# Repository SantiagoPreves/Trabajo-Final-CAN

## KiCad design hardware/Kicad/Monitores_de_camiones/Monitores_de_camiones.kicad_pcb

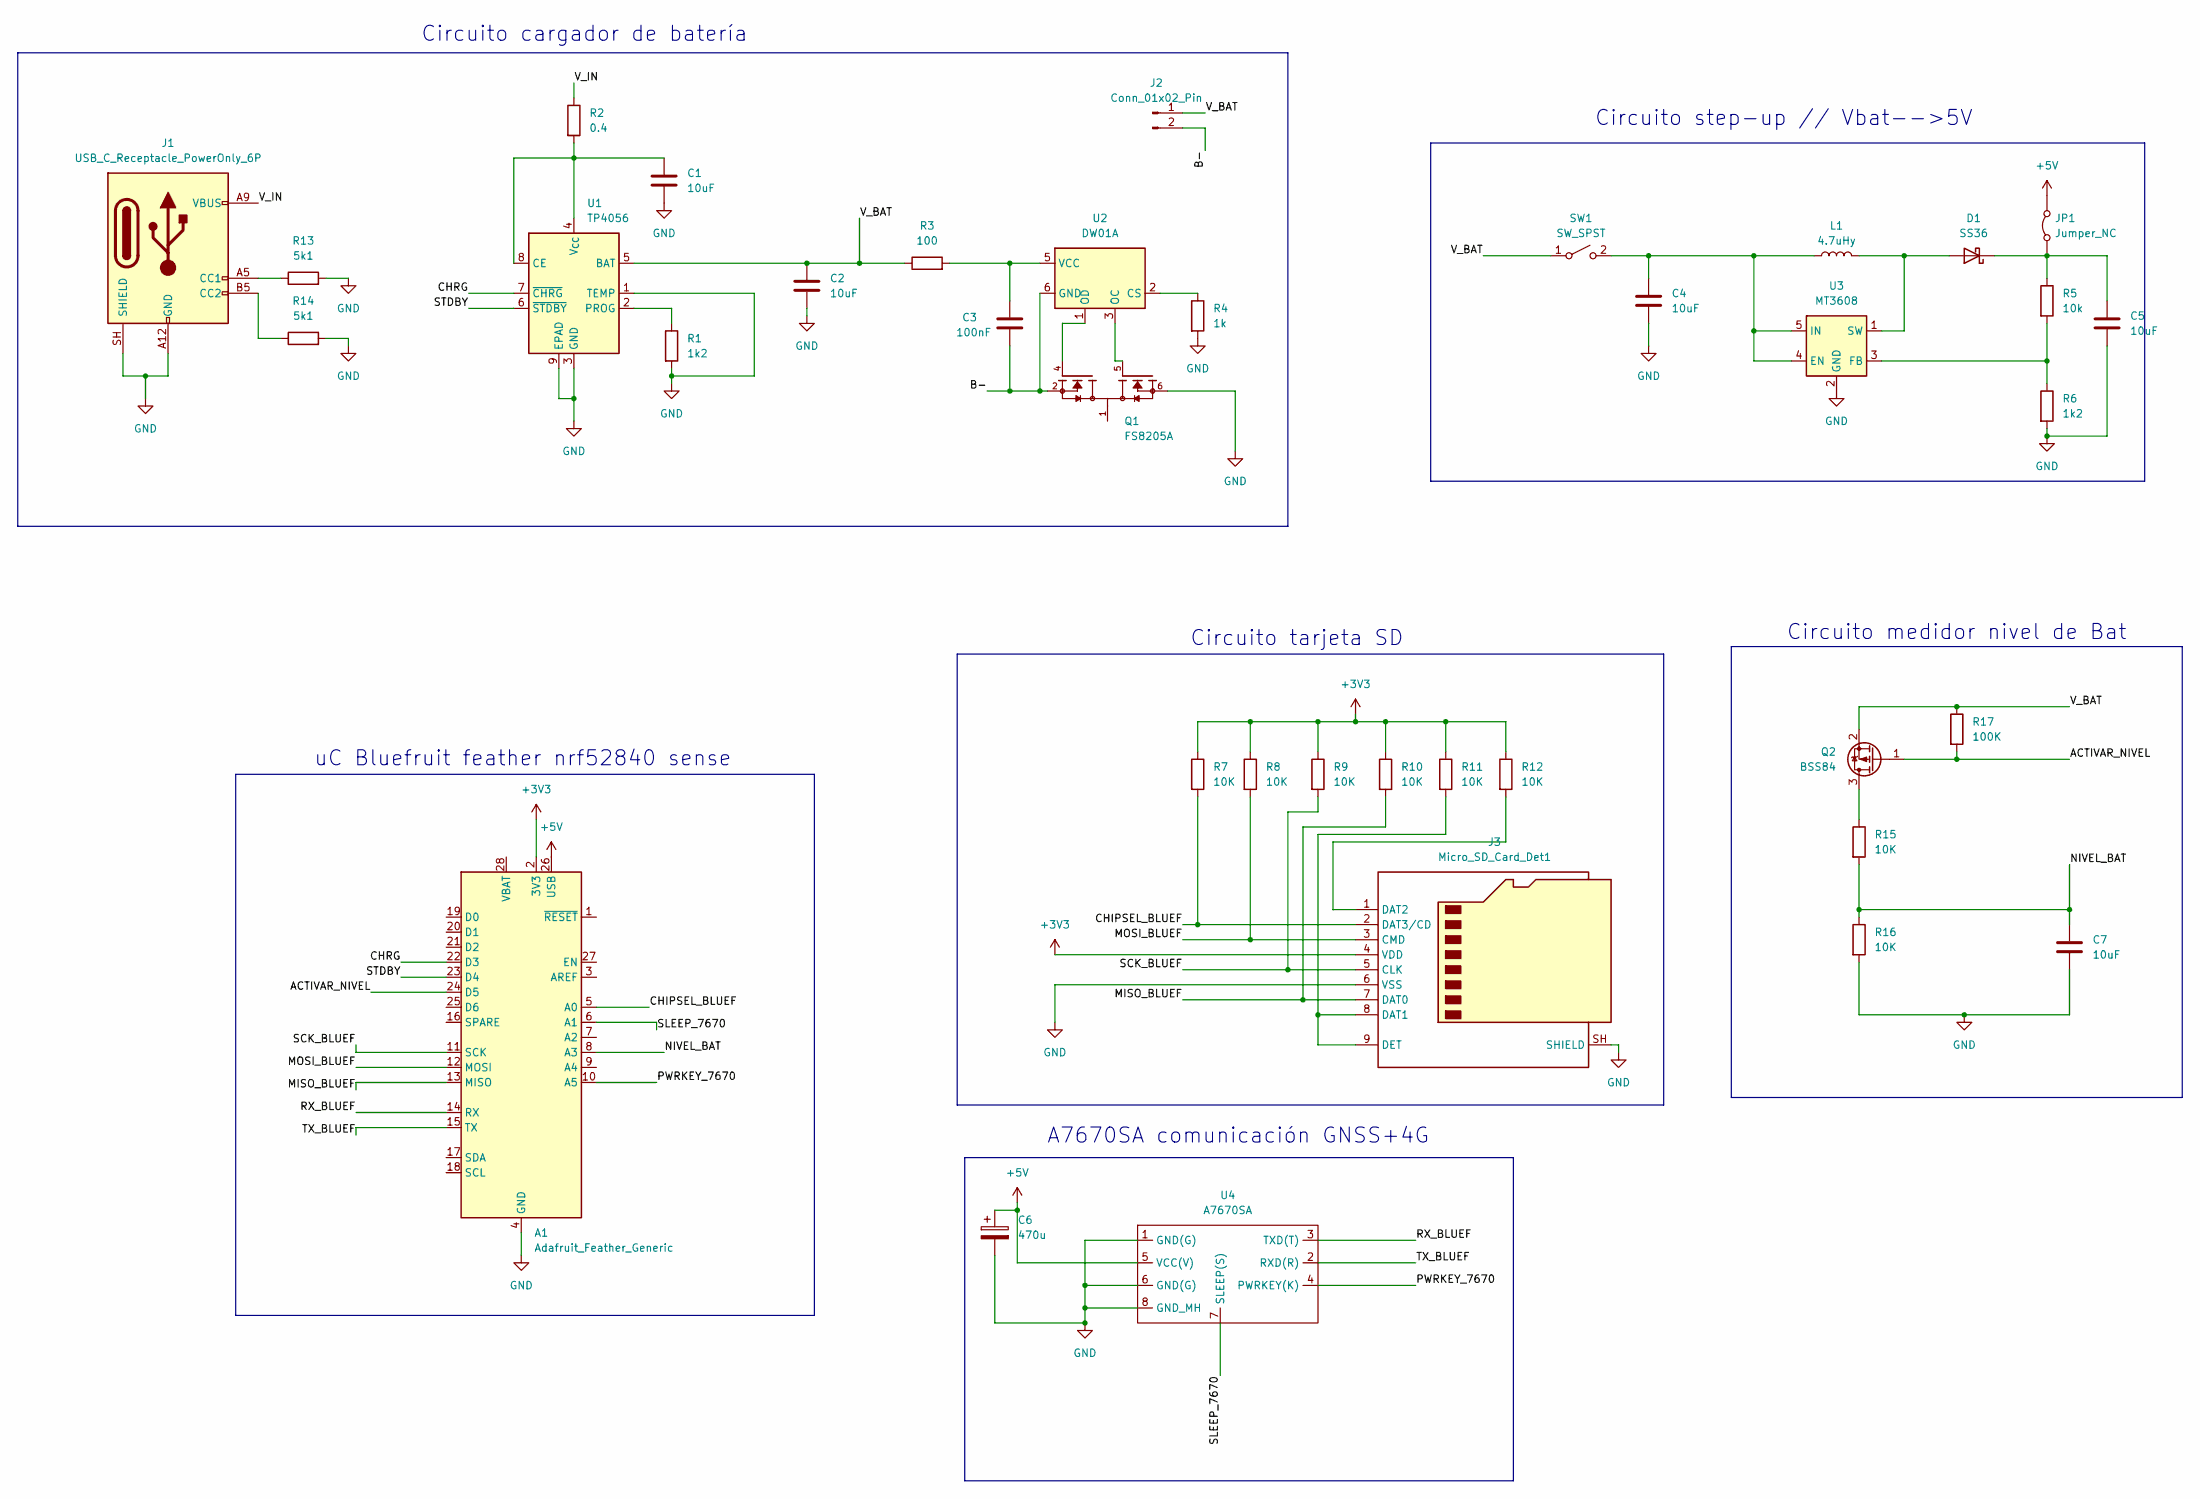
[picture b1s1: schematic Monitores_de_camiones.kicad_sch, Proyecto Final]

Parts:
A1: Adafruit_Feather_Generic; Adafruit_Feather
C1, C2, C7: 10uF; C_0805_2012Metric_Pad1.18x1.45mm_HandSolder
C3: 100nF; C_0805_2012Metric_Pad1.18x1.45mm_HandSolder
C4, C5: 10uF; C_1206_3216Metric_Pad1.33x1.80mm_HandSolder
C6: 470u; CP_Elec_6.3x5.2
D1: SS36; D_SMA
J1: USB_C_Receptacle_PowerOnly_6P; USB_C_Receptacle_GCT_USB4125-xx-x-0190_6P_TopMnt_Horizontal
J2: Conn_01x02_Pin; Molex_KK-254_AE-6410-02A_1x02_P2.54mm_Vertical
J3: Micro_SD_Card_Det1; microSD_HC_Hirose_DM3AT-SF-PEJM5
JP1: Jumper_NC; PinHeader_1x02_P2.54mm_Vertical
L1: 4.7uHy; L_Wuerth_WE-PDF_Handsoldering
Q1: FS8205A; FS8205A_TSSOP-8; PARTREV 1.7
Q2: BSS84; SOT-23
R1, R6: 1k2; R_0805_2012Metric_Pad1.20x1.40mm_HandSolder
R2: 0.4; R_0805_2012Metric_Pad1.20x1.40mm_HandSolder
R3: 100; R_0805_2012Metric_Pad1.20x1.40mm_HandSolder
R4: 1k; R_0805_2012Metric_Pad1.20x1.40mm_HandSolder
R5: 10k; R_0805_2012Metric_Pad1.20x1.40mm_HandSolder
R7, R8, R9, R10, R11, R12, R15, R16: 10K; R_0805_2012Metric_Pad1.20x1.40mm_HandSolder
R13, R14: 5k1; R_0805_2012Metric_Pad1.20x1.40mm_HandSolder
R17: 100K; R_0805_2012Metric_Pad1.20x1.40mm_HandSolder
SW1: SW_SPST; PinHeader_1x02_P2.54mm_Vertical
U1: TP4056; SOIC-8-1EP_3.9x4.9mm_P1.27mm_EP2.41x3.3mm_ThermalVias
U2: DW01A; SOT-23-6
U3: MT3608; SOT-23-6
U4: A7670SA

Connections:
+3V3: A1.2 (3V3), J3.4 (VDD), R7.1, R8.1, R9.1, R10.1, R11.1, R12.1
+5V: A1.26 (USB), C6.1, JP1.2 (B), U4.5 (VCC(V))
/ACTIVAR_NIVEL: A1.24 (D5), Q2.1 (G), R17.2
/B-: C3.2, J2.2, Q1.2, Q1.3, U2.6 (GND)
/CHIPSEL_BLUEF: A1.5 (A0), J3.2 (DAT3/CD), R7.2
/CHRG: A1.22 (D3), U1.7 (~CHRG)
/MISO_BLUEF: A1.13 (MISO), J3.7 (DAT0), R10.2
/MOSI_BLUEF: A1.12 (MOSI), J3.3 (CMD), R8.2
/NIVEL_BAT: A1.8 (A3), C7.1, R15.2, R16.1
/PWRKEY_7670: A1.10 (A5), U4.4 (PWRKEY(K))
/RX_BLUEF: A1.14 (RX), U4.3 (TXD(T))
/SCK_BLUEF: A1.11 (SCK), J3.5 (CLK), R9.2
/SLEEP_7670: A1.6 (A1), U4.7 (SLEEP(S))
/STDBY: A1.23 (D4), U1.6 (~STDBY)
/TX_BLUEF: A1.15 (TX), U4.2 (RXD(R))
/V_BAT: C2.1, J2.1, Q2.2 (S), R3.1, R17.1, SW1.1 (A), U1.5 (BAT)
/V_IN: J1.A9 (VBUS), J1.B9 (VBUS), R2.1
GND: A1.4 (GND), C1.2, C2.2, C4.2, C5.2, C6.2, C7.2, J1.A12 (GND), J1.B12 (GND), J1.SH (SHIELD), J3.6 (VSS), J3.SH (SHIELD), Q1.6, Q1.7, R1.2, R4.2, R6.2, R13.2, R14.2, R16.2, U1.1 (TEMP), U1.3 (GND), U1.9 (EPAD), U3.2 (GND), U4.1 (GND(G)), U4.6 (GND(G)), U4.8 (GND_MH)
unnamed: D1.2 (A), L1.2, U3.1 (SW)
unnamed: C5.1, D1.1 (K), JP1.1 (A), R5.1
unnamed: J1.A5 (CC1), R13.1
unnamed: J1.B5 (CC2), R14.1
unnamed: J3.8 (DAT1), J3.9 (DET), R11.2
unnamed: J3.1 (DAT2), R12.2
unnamed: Q1.1, Q1.8
unnamed: Q2.3 (D), R15.1
unnamed: C4.1, L1.1, SW1.2 (B), U3.4 (EN), U3.5 (IN)
unnamed: C1.1, R2.2, U1.4 (V_{CC}), U1.8 (CE)
unnamed: R1.1, U1.2 (PROG)
unnamed: R4.1, U2.2 (CS)
unnamed: Q1.5, U2.3 (OC)
unnamed: Q1.4, U2.1 (OD)
unnamed: C3.1, R3.2, U2.5 (VCC)
unnamed: R5.2, R6.1, U3.3 (FB)

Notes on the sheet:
A7670SA comunicación GNSS+4G
Circuito tarjeta SD
Circuito cargador de batería
Circuito medidor nivel de Bat
Circuito step-up // Vbat-->5V
uC Bluefruit feather nrf52840 sense

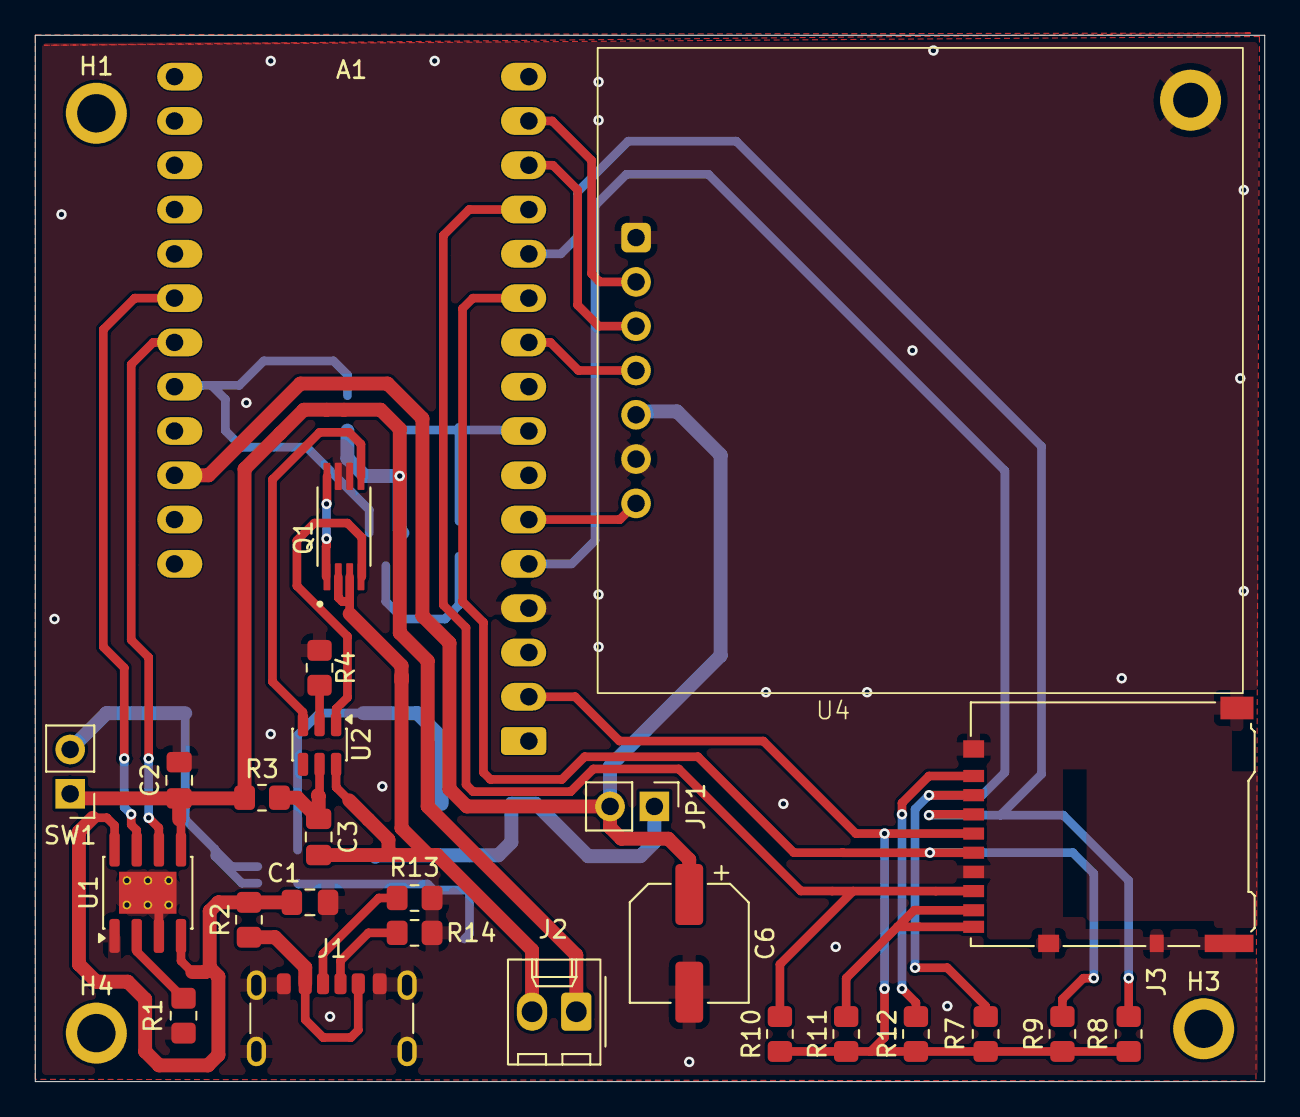
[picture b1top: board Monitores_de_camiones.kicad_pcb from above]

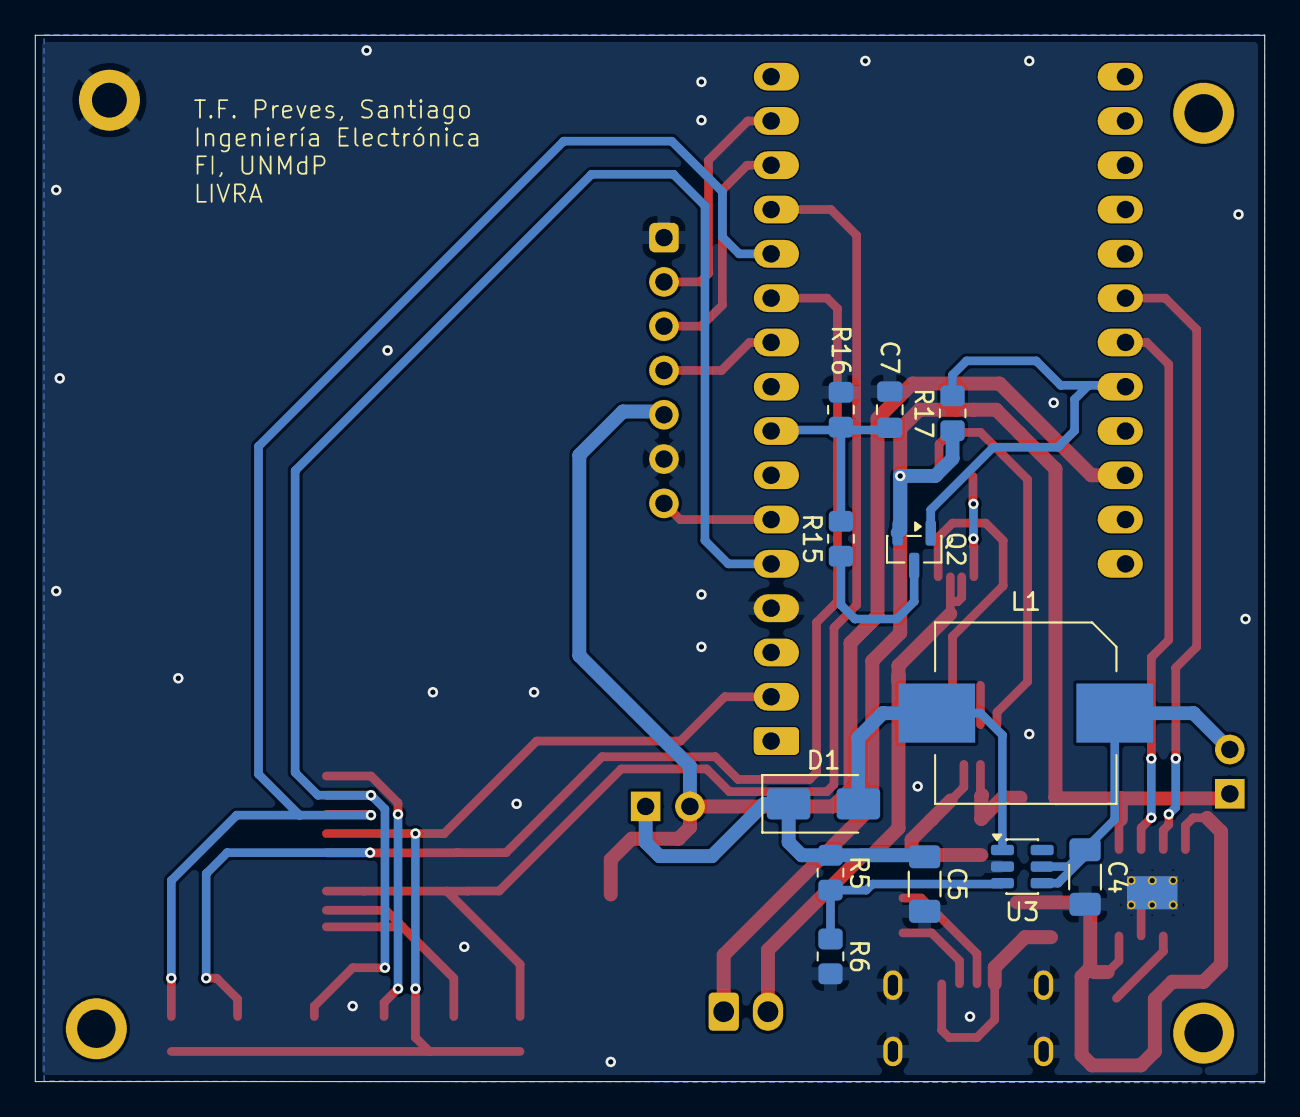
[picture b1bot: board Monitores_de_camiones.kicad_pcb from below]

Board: 2 copper layers, 70.5 x 60.0 mm, 41 parts (12 on the bottom side), 34 nets.

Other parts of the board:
H1, H3, H4: MountingHole_2.2mm_M2_ISO7380_Pad

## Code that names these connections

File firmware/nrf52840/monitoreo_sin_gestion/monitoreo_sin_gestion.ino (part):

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//  D5 habilita el divisor V_BAT -> R15 -> NIVEL_BAT -> R16 -> GND a
//  través del MOSFET Q2 (canal P, lado alto). A3 lee la tensión.
// ============================================================
#define PIN_ACTIVAR_NIVEL  12     // D5
#define PIN_NIVEL_BAT      A3

// Vbat = Vadc * (R15 + R16) / R16
#define DIV_R_TOP   10000.0f    // R15
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// ============================================================
//  ESTADO DE CARGA (TP4056: salidas open-drain activas en bajo)
// ============================================================
#define PIN_CHRG    10  // D3
#define PIN_STDBY   11  // D4

bool cargando       = false;
bool cargaCompleta  = false;
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// ============================================================
//  A7670SA - PWRKEY y SLEEP
// ============================================================
#define PIN_PWRKEY_7670  A5
#define PIN_SLEEP_7670   A1

// ============================================================
//  MQTT
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  Serial.println(mqttClientID);

  // PINES
  pinMode(PIN_ACTIVAR_NIVEL, OUTPUT);
  digitalWrite(PIN_ACTIVAR_NIVEL, NIVEL_INACTIVO);

  pinMode(PIN_CHRG,  INPUT_PULLUP);
  pinMode(PIN_STDBY, INPUT_PULLUP);

  pinMode(LED_BUILTIN, OUTPUT);
  digitalWrite(LED_BUILTIN, LOW);

  pinMode(PIN_SLEEP_7670, OUTPUT);
  digitalWrite(PIN_SLEEP_7670, LOW);   // LOW = despierto

  pinMode(PIN_PWRKEY_7670, OUTPUT);
  digitalWrite(PIN_PWRKEY_7670, HIGH);

  // ADC: referencia y resolución
  analogReference(AR_INTERNAL);   // 0.6V ref + gain 1/6 -> fondo de escala 3.6V
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// ============================================================
float leerNivelBateria()
{
  digitalWrite(PIN_ACTIVAR_NIVEL, NIVEL_ACTIVO);
  delay(BAT_SETTLE_MS);

  uint32_t acum = 0;
  for (int i = 0; i < BAT_OVERSAMPLE; i++) acum += analogRead(PIN_NIVEL_BAT);
  float lectura = (float)acum / (float)BAT_OVERSAMPLE;

  digitalWrite(PIN_ACTIVAR_NIVEL, NIVEL_INACTIVO);

  float vAdc = (lectura / ADC_MAX) * ADC_VREF;
  float vBat = vAdc * DIV_RATIO * CAL_BAT;
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// ============================================================
void leerEstadoCarga()
{
  cargando      = (digitalRead(PIN_CHRG)  == LOW);
  cargaCompleta = (digitalRead(PIN_STDBY) == LOW);
}

// ============================================================
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// ============================================================
void pulsarPWRKEY_7670()
{
  digitalWrite(PIN_PWRKEY_7670, HIGH);
  delay(100);
  digitalWrite(PIN_PWRKEY_7670, LOW);
  delay(1000);
  digitalWrite(PIN_PWRKEY_7670, HIGH);
  delay(3000);
}

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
